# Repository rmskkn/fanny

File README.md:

# Fanny — a USB PWM fan controller

A USB-controlled carrier board for an STM32F103C8T6 "Blue Pill" module. It
drives four 12 V PC fans and reads four analog sensors. The module shows up
on the host as a USB CDC serial port (`/dev/ttyACM*` or `COMx`).

## Key features

- **4 independent fan channels.** Each one switches between `pwm` (4-pin
  signal control) and `dc` (3-pin supply chopping) at runtime.
- **4 analog inputs** for NTC or voltage sensors plus 12 V rail sensing. All
  share one ADC scan with mV conversion.
- **Tach and stall detection** on all 4 channels. Fans 1-3 are counted by
  hardware timers, fan 4 by a level-checked interrupt.
- **Hardware failsafe by design.** Every control line rests in its "fan on"
  state by default, held there by pull resistors alone. A fan runs at
  100% on power-up, after a crash, or with the MCU pulled out. No firmware
  or host required.
- **Per-channel and board-level PTC fusing** plus a 12 V TVS.
- **Text protocol over USB CDC.** Comes with a Python CLI (`fanctl.py`) and
  a daemon (`fancontrold.py`) for temperature or GPU-temperature curves.

## Repository structure

```
.
├── firmware/          MCU firmware
│   ├── Core/          clocks, SysTick, linker script, board pin map
│   ├── Drivers/       libopencm3 submodule
│   ├── USB_DEVICE/    USB CDC-ACM device
│   ├── App/           fan, pwm, tach, protocol, thermal, safety
│   └── tests/         host-side unit tests
├── hardware/
│   ├── kicad/         schematic, symbol lib, board
│   ├── bom.csv        bill of materials
│   ├── pcb_3d.png     3D render of the placed board
│   ├── pcb_top.png    placement plot seen from the top
│   └── datasheets/    links to the key datasheets
└── host/              fanctl.py command-line client (pyserial)
```

## Prerequisites

KiCad 10.0.7, arm-none-eabi-gcc, OpenOCD, and Python 3 with pyserial:

```sh
# Arch
sudo pacman -S kicad arm-none-eabi-gcc arm-none-eabi-newlib openocd python python-pyserial

# Ubuntu 24.04
sudo add-apt-repository ppa:kicad/kicad-10.0-releases
sudo apt update
sudo apt install kicad gcc-arm-none-eabi openocd python3 python3-serial
```

You also need an ST-Link V2 programmer wired to the Blue Pill's SWD header
to flash firmware.

## Hardware design

### Block overview

```mermaid
flowchart LR
    classDef power fill:#fde3d8,stroke:#e2572b,color:#111
    classDef usb fill:#dbe7ff,stroke:#2f6fed,color:#111
    classDef mcu fill:#e8d7f5,stroke:#5b4b8a,color:#111
    classDef pwm fill:#d7f5df,stroke:#2f9e44,color:#111
    classDef dcmode fill:#fdecc3,stroke:#c77f00,color:#111
    classDef tach fill:#d7f5df,stroke:#0f9b8e,color:#111
    classDef analog fill:#fbd9e8,stroke:#c2255c,color:#111

    subgraph PWR["Power 12 V"]
        PSU["12 V PSU"] --> J1["J1 Mate-N-Lok"] --> F1["F1 PTC 2.5A"] --> D1["D1 TVS"] --> V12["+12V"]
        V12 --> F25["F2..F5 1.1A PTC x4"] --> FANV["fan +12V x4"]
        V12 --> DIV["47k/10k divider"] --> PB0["PB0 ADC"]
    end

    subgraph USB3V3["USB / 3V3"]
        USB["USB via Blue Pill microB"] --> P5V["+5V"] --> LDO["Blue Pill LDO"] --> V33["+3V3"] --> FB1["FB1"] --> V33A["+3V3A"]
    end

    subgraph MCU["Blue Pill module on J2 and J3"]
        subgraph PWMSIG["PWM signal on fan pin 4"]
            TIM4["TIM4 PB6..PB9 25kHz"] --> BSS["BSS138 open drain"] --> FPWM["fan PWM pin"]
        end
        subgraph DCMODE["DC-mode motor switch per channel"]
            QINV["Q_inv BSS138"] --> QEN["Q_en gated by FANn_DCEN"] --> QPNP["Q_pnp AO3401A pull-up"] --> QHS["Q_hs AO3401A"] --> FSW["fan +12V motor switch"]
            GPIO["PA6 PA7 PA8 PB1 GPIO"] --> QEN
        end
        TIM4 -. reuses PWM signal .-> QINV
        subgraph TACHLANE["Tach"]
            FT["fan tach"] --> PU["10k pull-up"] --> RC["RC filter"] --> EXTI["TIM1/2/3 counters, EXTI PB15"]
        end
    end

    subgraph ANALOG["Analog inputs"]
        SENS["sensors"] --> RCB["1k + 100n + BAT54S"] --> ADC["PA0..PA5 ADC x6"]
    end

    class PSU,J1,F1,D1,V12,F25,FANV,DIV power
    class PB0 mcu
    class USB,P5V,LDO,V33,FB1,V33A usb
    class TIM4,BSS,FPWM pwm
    class QINV,QEN,QPNP,QHS,FSW,GPIO dcmode
    class FT,PU,RC,EXTI tach
    class SENS,RCB,ADC analog
```

### Pin map

| Function | Pins | Peripheral |
|---|---|---|
| Fan 1–4 PWM signal and the motor-switch chop signal in DC mode | PB6 PB7 PB8 PB9 | TIM4 CH1–4 at 25 kHz |
| Fan 1–4 DC-mode enable | PA6 PA7 PA8 PB1 | plain push-pull GPIO |
| Fan 1–3 tach | PA9 PA15 PB5 | TIM1 CH2, TIM2 CH1 (partial remap 1), TIM3 CH2 (partial remap), each in external clock mode counting falling edges in hardware |
| Fan 4 tach | PB15 | EXTI15 on both edges, counted only on a real high-to-low level change |
| AIN1–AIN4 | PA0–PA3 | ADC1 IN0–IN3 |
| 12 V sense | PB0 | ADC1 IN8 |

### Compatibility

Verified against the [Intel 4-wire PWM fan spec rev 1.2](https://www.konilabs.net/docs/standards/fan/intel_4wire_pwm_fans_specs_rev1_2.pdf):

| Spec requirement | Board implementation | Status |
|---|---|---|
| Pinout of GND then +12 V then tach then PWM | `Fan_4pin` header wired in that order | Match |
| PWM must be open-drain or open-collector with the fan pulling up | BSS138 open-drain transistor where the MCU only sinks | Match |
| PWM frequency between 21 kHz and 28 kHz with 25 kHz nominal | TIM4 at 72 MHz / 2880 which is exactly 25.000 kHz | Match |
| A released PWM line must run the fan at full speed | 100 kΩ pull-down holds the transistor off until firmware drives it | Match |
| Tach must be open-collector and pulled up at 2 pulses per rev | 10 kΩ pull-up to 3.3 V with `TACH_PULSES_PER_REV = 2` in firmware | Match |
| Tach pull-up rail of 5 V or less into a tolerant input | Pulled to 3.3 V. PA9, PA15 and PB15 are 5 V tolerant; PB5 is not, so fan 3 needs the 3.3 V pull-up | Match |

### Analog inputs (AIN1–AIN4)

Each input is a 3-pin header carrying 3V3A and SIG and GND. The conditioning
chain works like this:

- A 10 kΩ pull-up to 3V3A. Together with a 10 kΩ NTC to GND it forms a
  ratiometric temperature divider. Leave it unfitted for voltage-output
  sensors.
- A 1 kΩ series resistor and 100 nF to GND for anti-aliasing and sample
  charge.
- A BAT54S clamp to GND and 3V3A. PA0–PA3 are **not** 5 V tolerant.

The ADC references VDDA. The firmware measures VREFINT so it can report
millivolts corrected for the actual supply voltage.

#### Choosing an NTC

The on-board pull-up is 10 kΩ, matched to a 10 kΩ NTC with B=3950 (`ntc_r25 =
10000`, `ntc_beta = 3950` in the fan daemon config, both already the
defaults). Any bare 2-wire 10 kΩ/B3950 probe plugs straight in, SIG and GND,
no third wire needed — this is what the probe bundled with the
[Skip0ner 1X4L fan-1248 conf v1](https://skiponer.com/1x4l-pwm-fan-controller-manual/)
module is. Expected mV at a given temperature:
`hardware/datasheets/NTC-10k-B3950 Response Curve.md`, taken from the
10k/3950 column of Focusensing's
[10k thermistor reference chart](https://www.focusensing.com/10k-thermistor-chart-type-2-vs-type-3-vs-3950-tables_n196).
The onboard autocurve mode (`auto on`) uses the same table, baked into
`firmware/App/ntc_calib.h`.

A different R25 needs a matching pull-up swap, since the pull-up sets both
the divider's output range and the firmware's calibration constant: match
`ntc_r25` (host) and `ntc_calib_ain1..4` (firmware) to the new part's R25 and
B, and re-check `fanctl.py get`'s `ain N mv` against a known temperature
before trusting the curve.

### Power

- **12 V input:** a screw terminal followed by a PTC that holds 2.5 A and
  then an SMBJ13A TVS. Reversed polarity makes the TVS conduct and that trips
  the PTC.
- **Module supply:** USB only. The board carries no 5 V or 3.3 V regulator.
  The LDO on the Blue Pill makes 3.3 V from USB VBUS.
- **12 V monitoring:** a 47 kΩ/10 kΩ divider into PB0. Full scale lands near
  18.8 V.
- **USB:** the micro-B connector of the Blue Pill and nothing else. The
  carrier has no USB connector or header or ESD protection of its own. The
  firmware pulls D+ low for 10 ms at boot to force the host to re-enumerate.

## BOM list

The full bill of materials is in [`hardware/bom.csv`](hardware/bom.csv).

## Firmware

### Build

```sh
git clone --recurse-submodules git@github.com:rmskkn/fanny.git
cd fanny
make                 # firmware/build/fanny.elf, .bin (~11.5 KiB flash)
make flash           # flash fanny.bin, OpenOCD + ST-Link over SWD
make test            # host-side protocol and conversion tests
```

The first `make` builds libopencm3 for STM32F1 only. It also runs
`git submodule update --init` when the clone has no submodule checkout. The
same targets work from inside `firmware/`.

`make flash` wraps this OpenOCD call, with an ST-Link programmer on the
Blue Pill's SWD header. `fanny.bin` is a raw image with no load address, so
one is given on the command line, the start of flash on this MCU:

```sh
openocd -f interface/stlink.cfg -f target/stm32f1x.cfg \
    -c "program firmware/build/fanny.bin verify reset exit 0x08000000"
```

`fanny.elf` still builds alongside it (`make` keeps producing both), kept
for `arm-none-eabi-size` and debugging, but flashing only ever needs the bin.

### Failsafe behaviour

All fans run at 100 % whenever the controller is not in control and that holds
in both `pwm` and `dc` mode. Fan power comes straight from 12 V so this needs
nothing but 12 V present. The PWM signal line and the motor switch and the
DC-mode enable all rest in their "fan on" state. Pin 4 is released and
`R_gpd` holds the motor switch on and `R_dcen` holds the enable off. Either
mode reaches 100 % the same way.

| Case | Result |
|---|---|
| Power-up before the first command from the host | 100 % |
| USB unplugged or host powered off | Module unpowered and both switches rest on at 100 % |
| Module pulled out of its socket | Both switches rest on at 100 % |
| Supply sags below the reset threshold of the STM32 near 1.9 V | MCU held in reset and both switches rest on at 100 % |
| Firmware hangs | Watchdog resets the MCU after 1 s and both switches rest on during reset at 100 % |
| No valid command for 10 s while the module is still powered | Firmware failsafe sets 100 % and the LED blinks fast and the mode stays unchanged |

Running `fanctl.py watch` or a control daemon keeps the 10 s timer from
expiring. A fan is flagged `stall=1` when its duty sits above 0 but its tach
reads 0 RPM for 3 s. Fans without a tach wire always show this flag.

### Host commands

The protocol is text over USB CDC and the baud rate is ignored. Each command
is one line ending in `\n` and each reply ends with `ok` or `err <reason>`.

```
> set 2 40          duty 0..100 for fan 1..4 or "all"
ok
> mode 3 dc         pwm (4-pin) | dc (3-pin)
ok
> get
fan 1 mode=pwm duty=100 rpm=1590 stall=0
fan 2 mode=pwm duty=40 rpm=780 stall=0
fan 3 mode=dc duty=100 rpm=1200 stall=0
fan 4 mode=pwm duty=100 rpm=0 stall=1
ain 1 raw=2047 mv=1649
...
v12 mv=12043
vdda mv=3302
mcu temp=31.4
failsafe=0
ok
> ping              keepalive
ok
```

## Host tool

```sh
pip install -r host/requirements.txt
python3 host/fanctl.py -p /dev/ttyACM0 get
python3 host/fanctl.py set all 50
python3 host/fanctl.py mode 3 dc
python3 host/fanctl.py watch -i 2
```

### Setting one fan

Use the fan number from 1 to 4 in place of `all`. Fan 1 is header J5 and fan
4 is header J8.

```sh
python3 host/fanctl.py set 1 50      # fan 1 to 50 %
python3 host/fanctl.py set 3 80      # fan 3 to 80 %
python3 host/fanctl.py set 4 0       # fan 4 to 0 % (some fans keep turning slowly)
python3 host/fanctl.py -p /dev/ttyACM1 set 2 40   # board on another port
```

- Each command sets one fan or all fans. Lists such as `1,2` and ranges such
  as `1-3` are not accepted.
- To check a fan run `python3 host/fanctl.py get` and read the
  `fan N mode=... duty=... rpm=...` line.
- Settings hold only while the host keeps talking to the board. When no
  command arrives for 10 s all fans return to 100 %. Keep `fanctl.py watch`
  or a control daemon running to hold the values.
- `mode <1-4|all> pwm|dc` picks the speed-control path for a channel: `pwm`
  for a 4-pin fan, `dc` for a 3-pin fan. It falls back to `pwm` at every
  boot and after every reconnect so the channel of a 3-pin fan needs
  `mode N dc` sent again each time.

The `FanController` class in `fanctl.py` can be imported to build a control
daemon. One example is a daemon that maps an NTC reading from `ain` onto a fan
duty. For a 10 kΩ NTC sitting on the 10 kΩ bias resistor the resistance is
R<sub>NTC</sub> = 10 kΩ × mV / (VDDA − mV).

### Fan control daemon

`host/fancontrold.py` is exactly that daemon. It reads an INI config shown in
`host/fancontrol.conf.example`. The config can set each of the four channels
to a constant duty or to a temperature curve driven by one AIN input or to a
curve driven by the temperature of an NVIDIA GPU through `sensor = gpuN` read
via `nvidia-smi` using the higher of the core and memory temperature. A
managed channel also takes `type = pwm` for the 4-pin default or `type = dc`
for a 3-pin fan. The daemon sends `mode` once at startup and again after every
reconnect because a firmware reset returns every channel to `pwm`. Every cycle
it re-sends the duty of each managed channel which doubles as the ping that
holds off the 10 s firmware failsafe. A channel with no `[fanN]` section is
left alone. `nvidia-smi` must be on `PATH` and no extra Python dependency is
needed.

For a `gpuN` sensor install the proprietary NVIDIA driver which provides
`nvidia-smi`:

```sh
# Arch
sudo pacman -S nvidia nvidia-utils

# Ubuntu 24.04
sudo apt install nvidia-driver-550
```

Reboot the machine to load the nvidia modules. Verify with
`nvidia-smi --query-gpu=index,temperature.gpu,temperature.memory --format=csv`.

```sh
cp host/fancontrol.conf.example ~/.config/fancontrol.conf
# edit ~/.config/fancontrol.conf for your sensors and curves
python3 host/fancontrold.py                 # foreground, Ctrl-C to stop
```

To run it as a systemd user service:

```sh
mkdir -p ~/.config/systemd/user
cp host/systemd/fancontrold.service ~/.config/systemd/user/
# edit ExecStart in that file to this repo's checkout path
systemctl --user daemon-reload
systemctl --user enable --now fancontrold.service
loginctl enable-linger "$USER"   # only if the board must run with no user session logged in
```

## Known limits

- **0 % doesn't stop every 4-pin fan in `pwm` mode** (fan-dependent). It does
  stop the fan in `dc` mode.
- **Duty 1-100 % maps to 10-100 % on the PWM line.** A Noctua NF-P12 PWM
  won't start below 10 % and stops below about 6 % even after a spin-up, so
  the firmware never sends less than 10 % unless you set 0 %. At 1 % that fan
  runs at about 200 rpm. Every other setting lands a little above its raw
  value: 50 % sends 55 %.
- **3-pin fans in `dc` mode won't start below ~30-40 % duty** (motor limit,
  not firmware). Set a curve minimum above it.
- **Fan 4 tach uses an interrupt, not a hardware counter.** Each counter
  needs a whole timer, and the STM32F103C8 has four: TIM1-TIM3 count fans
  1-3 and TIM4 makes the PWM. Fan 4 runs on EXTI15 with a pin-level check
  that ignores spikes shorter than the interrupt entry time (about 0.5 us).
  Longer glitches still count, and edges closer together than the handler
  runtime can merge.
- **JTAG is off** because fan 2 tach uses PA15. SWD on PA13/PA14 still
  flashes and debugs the board.
- **Tach under-reads in `dc` mode** since the fan is unpowered during the
  chopped-off phase. `stall` is only meaningful near 100 % duty.
- **25 kHz chop stresses a fan's input cap** but stays inaudible. All four
  `pwm` channels share one chop frequency.

## License

Copyright © 2026 Roman Skakun.

This project covers the hardware design files and the firmware and the host
tool. All of it is licensed under
[Creative Commons Attribution-NonCommercial-ShareAlike 4.0 International](LICENSE)
which is CC BY-NC-SA 4.0.

You may build and modify and share this design for personal and other
non-commercial purposes with attribution and under the same license.
Commercial use is not permitted without a separate written license from the
copyright holder. That includes selling assembled boards or bare PCBs or kits.

`firmware/Drivers/libopencm3` is a submodule under its own LGPL-3.0 license
and is not covered by the above.

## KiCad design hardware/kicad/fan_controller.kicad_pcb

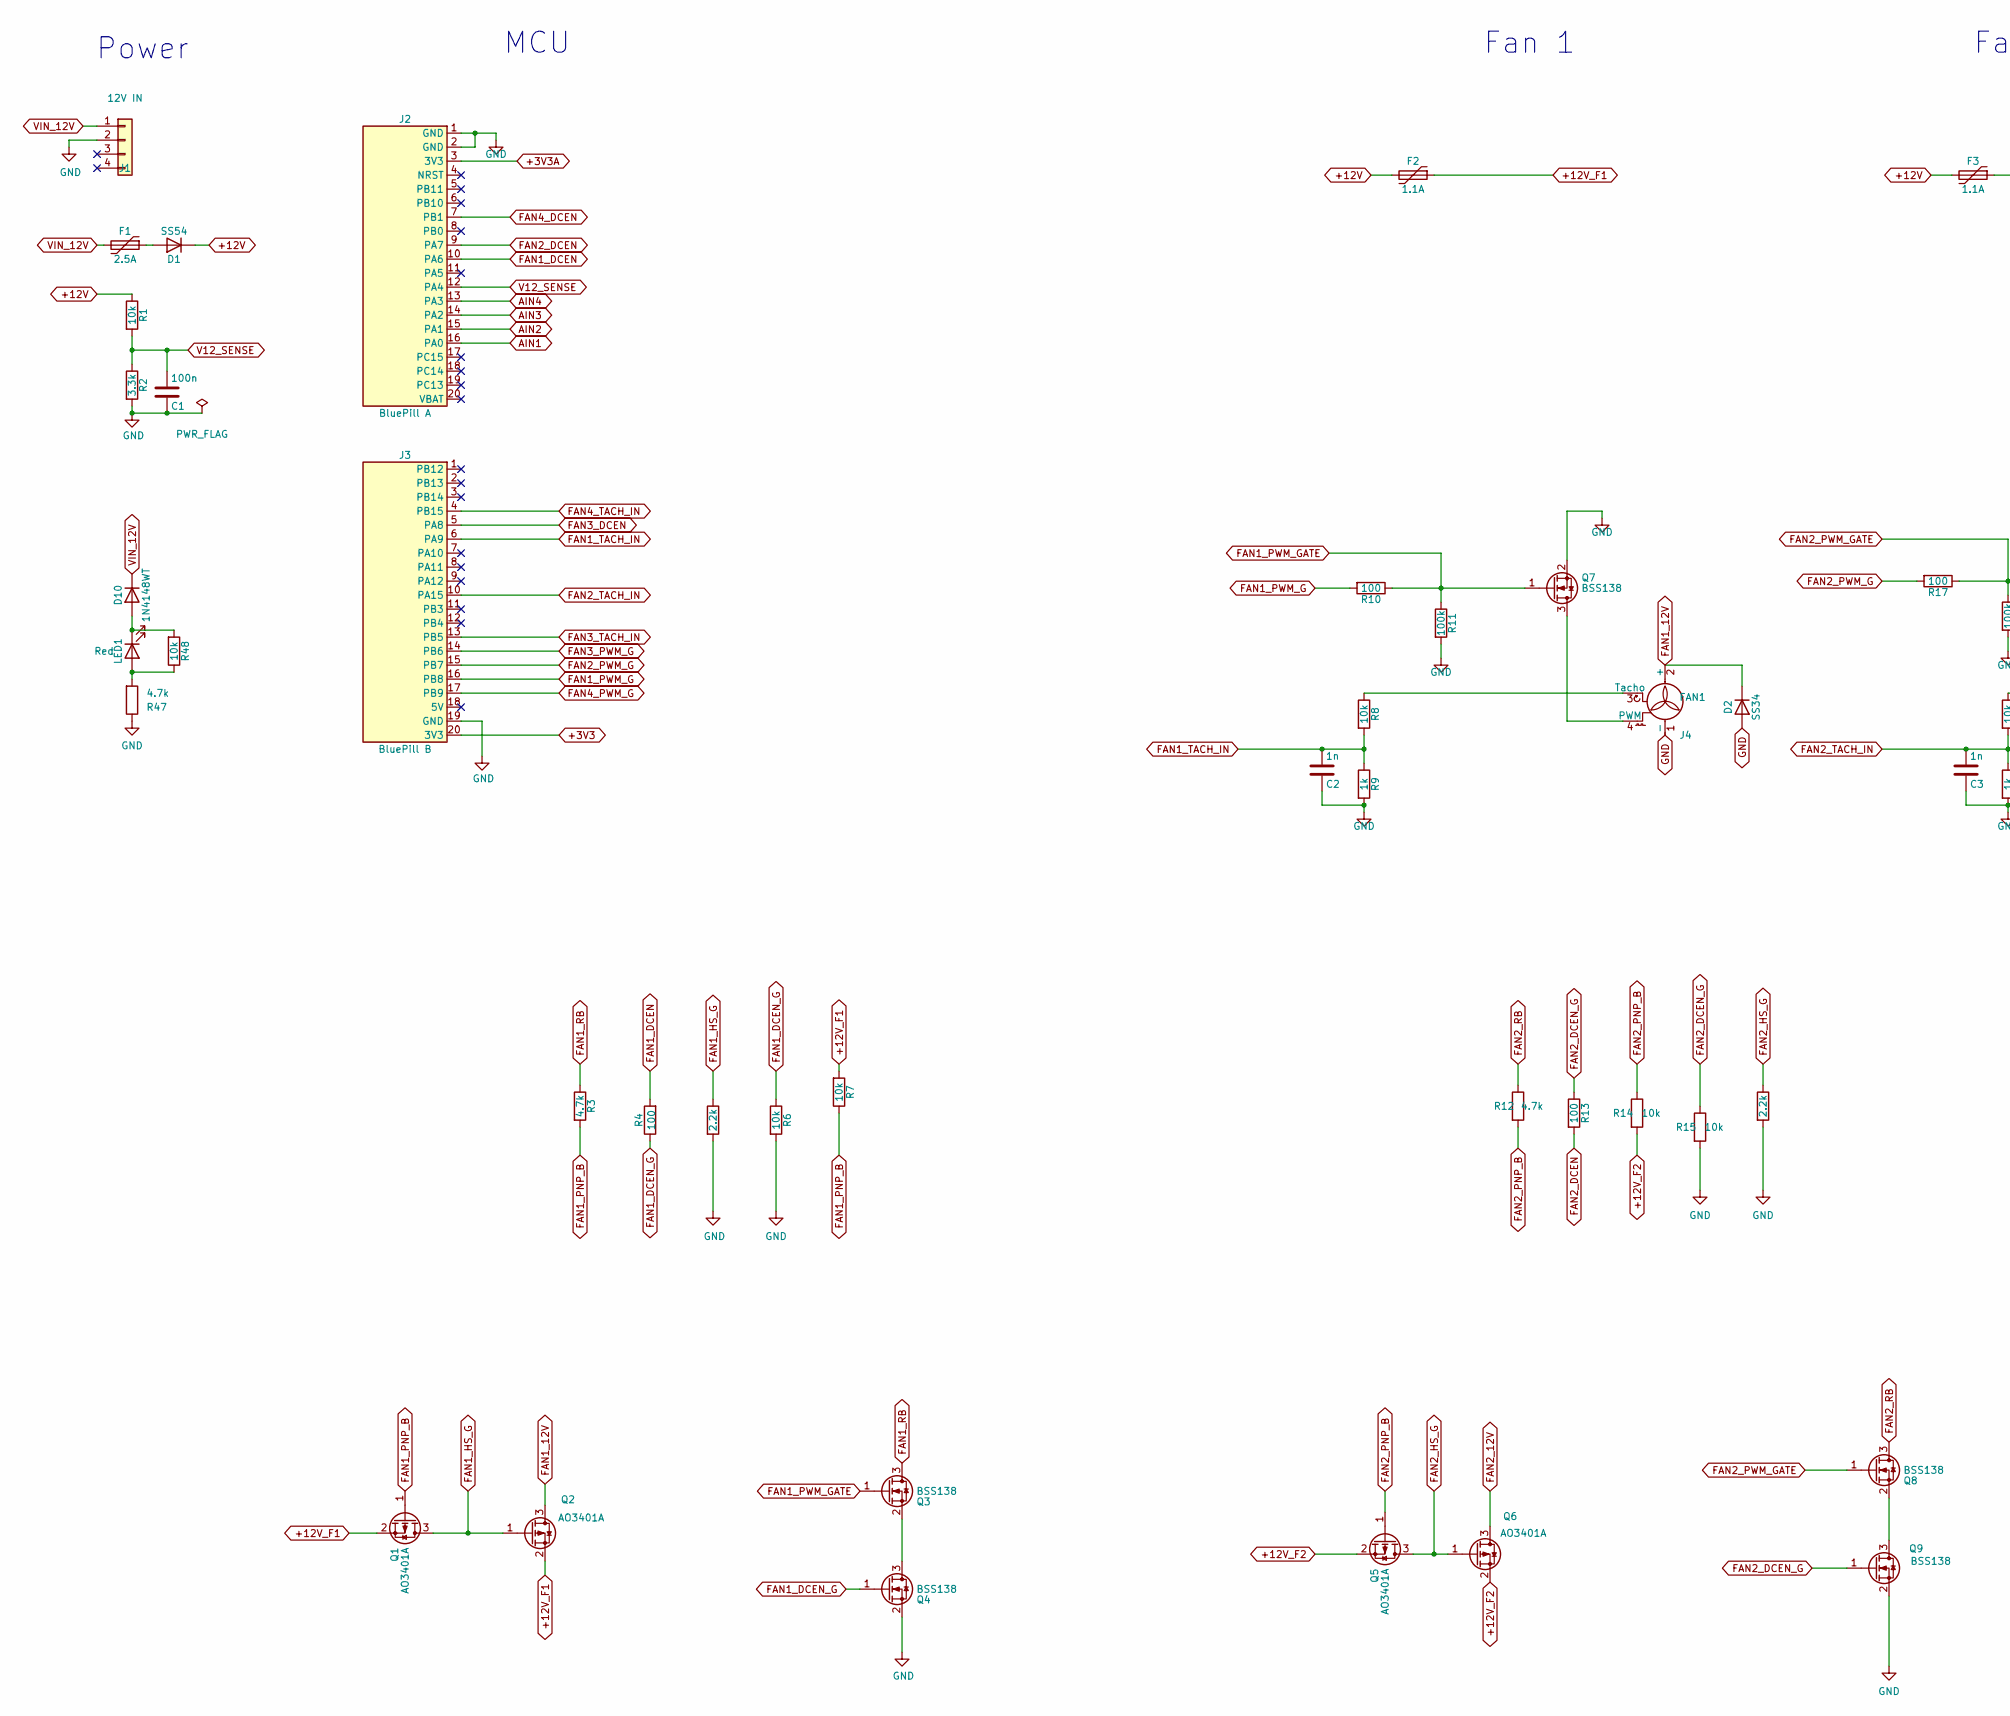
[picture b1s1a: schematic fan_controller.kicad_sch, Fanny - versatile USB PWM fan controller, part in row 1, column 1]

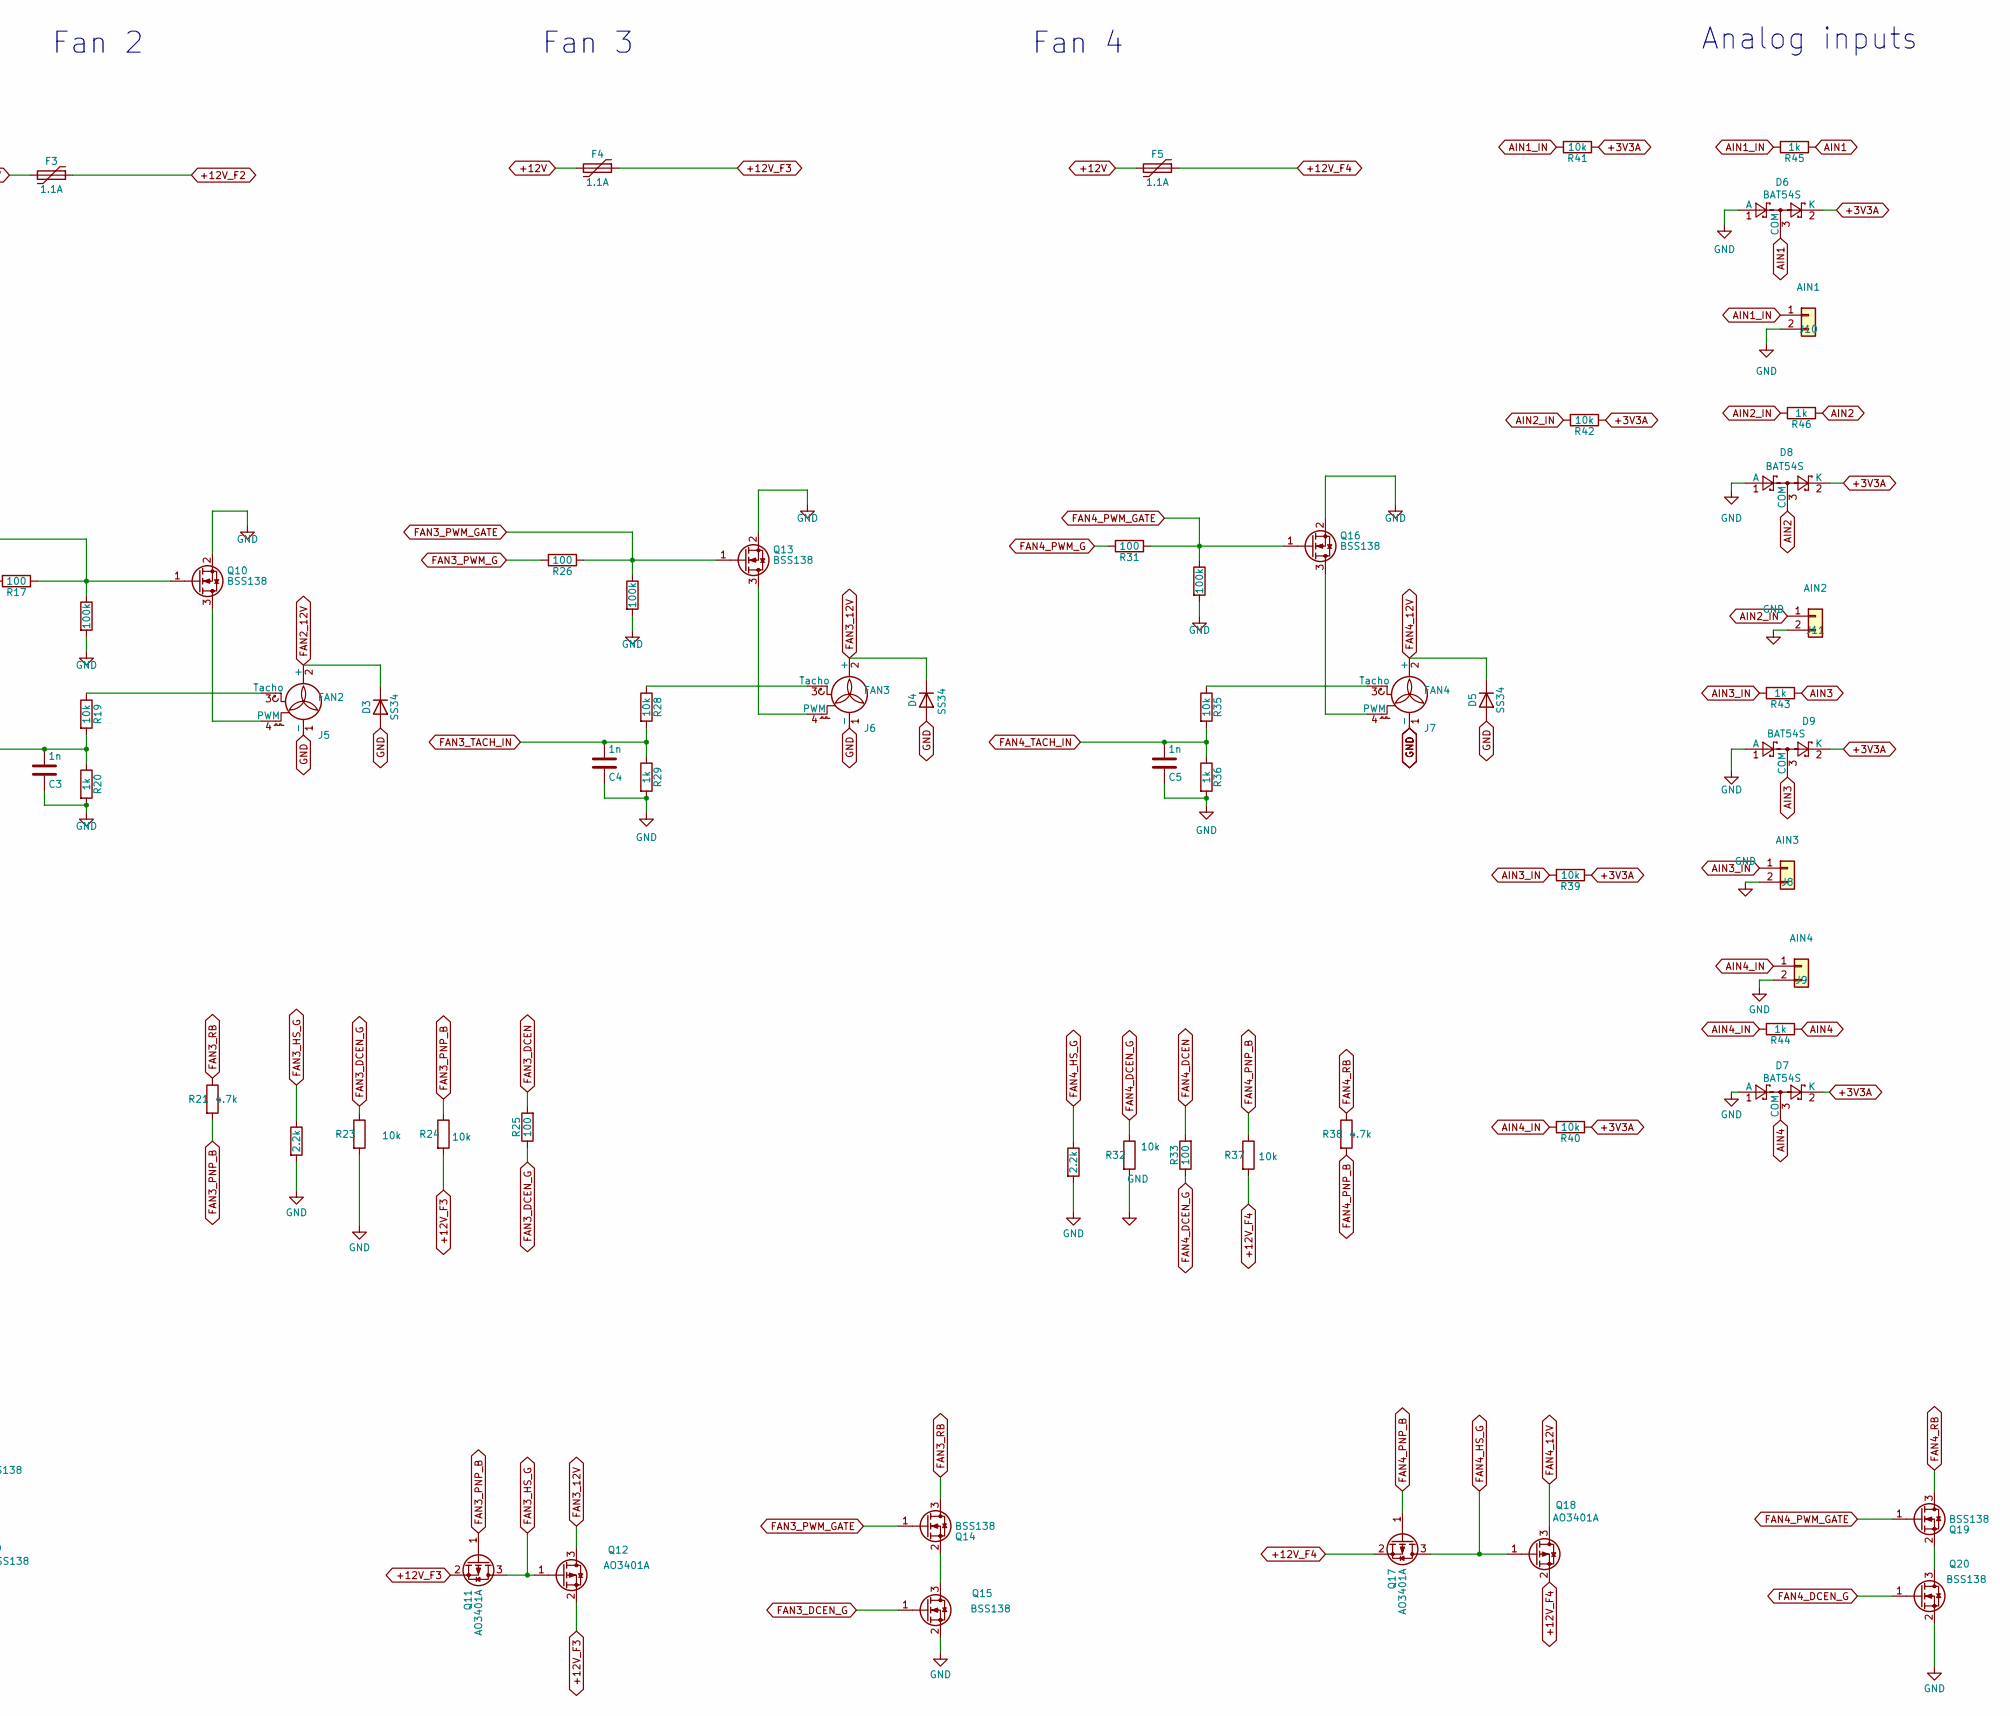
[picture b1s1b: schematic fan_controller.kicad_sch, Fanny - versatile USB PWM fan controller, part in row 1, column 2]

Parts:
C1: 100n; C_0603_1608Metric
C2, C3, C4, C5: 1n; C_0603_1608Metric
D1: SS54; D_SMB; MPN Littelfuse SMBJ13A
D2, D3, D4, D5: SS34; D_SMA; MPN SS34
D6, D7, D8, D9: BAT54S; SOT-23; MPN Nexperia BAT54S,215
D10: 1N4148WT; D_SOD-523
F1: 2.5A; Fuse_1812_4532Metric; MPN Bourns MF-MSMF250/16X-2
F2, F3, F4, F5: 1.1A; Fuse_1812_4532Metric; MPN Bourns MF-MSMF110/16-2
J1: 12V IN; ConnHeader_MateNLok_1x04_P5.08mm_Vertical; MPN TE Connectivity 350424-1
J2: BluePill A; PinSocket_1x20_P2.54mm_Vertical
J3: BluePill B; PinSocket_1x20_P2.54mm_Vertical
J4: FAN1; FanPinHeader_1x04_P2.54mm_Vertical; MPN Molex 47053-1000
J5: FAN2; FanPinHeader_1x04_P2.54mm_Vertical; MPN Molex 47053-1000
J6: FAN3; FanPinHeader_1x04_P2.54mm_Vertical; MPN Molex 47053-1000
J7: FAN4; FanPinHeader_1x04_P2.54mm_Vertical; MPN Molex 47053-1000
J8: AIN3; JST_PH_B2B-PH-K_1x02_P2.00mm_Vertical
J9: AIN4; JST_PH_B2B-PH-K_1x02_P2.00mm_Vertical
J10: AIN1; JST_PH_B2B-PH-K_1x02_P2.00mm_Vertical
J11: AIN2; JST_PH_B2B-PH-K_1x02_P2.00mm_Vertical
LED1: Red; LED_0603_1608Metric
Q1, Q2, Q5, Q6, Q11, Q12, Q17, Q18: AO3401A; SOT-23; MPN Alpha & Omega AO3401A
Q3, Q7, Q8, Q10, Q13, Q14, Q16, Q19: BSS138; SOT-23; MPN onsemi BSS138
Q4, Q9, Q15, Q20: BSS138; SOT-23
R1, R6, R7, R8, R14, R15, R19, R23, R24, R28, R32, R35, R37, R39, R40, R41, R42, R48: 10k; R_0603_1608Metric
R2: 3.3k; R_0603_1608Metric
R3, R12, R21, R38: 4.7k; R_0603_1608Metric
R4, R10, R13, R17, R25, R26, R31, R33: 100; R_0603_1608Metric
R5, R16, R22, R30: 2.2k; R_0603_1608Metric
R9, R20, R29, R36, R43, R44, R45, R46: 1k; R_0603_1608Metric
R11, R18, R27, R34: 100k; R_0603_1608Metric
R47: 4.7k; R_1206_3216Metric

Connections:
+3V3: J3.20 (3V3); also elsewhere on the board
+3V3A: D6.2 (K), D7.2 (K), D8.2 (K), D9.2 (K), J2.3 (3V3), R39.1, R40.1, R41.1, R42.1; also elsewhere on the board
+12V: D1.1 (K), F2.2, F3.2, F4.2, F5.2, R1.1
+12V_F1: F2.1, Q1.2 (S), Q2.2 (S), R7.2
+12V_F2: F3.1, Q5.2 (S), Q6.2 (S), R14.2
+12V_F3: F4.1, Q11.2 (S), Q12.2 (S), R24.2
+12V_F4: F5.1, Q17.2 (S), Q18.2 (S), R37.2
AIN1: D6.3 (COM), J2.16 (PA0), R45.1
AIN1_IN: J10.1, R41.2, R45.2
AIN2: D8.3 (COM), J2.15 (PA1), R46.1
AIN2_IN: J11.1, R42.2, R46.2
AIN3: D9.3 (COM), J2.14 (PA2), R43.1
AIN3_IN: J8.1, R39.2, R43.2
AIN4: D7.3 (COM), J2.13 (PA3), R44.1
AIN4_IN: J9.1, R40.2, R44.2
FAN1_12V: D2.1 (K), J4.2 (+), Q2.3 (D)
FAN1_DCEN: J2.10 (PA6), R4.2
FAN1_DCEN_G: Q4.1 (G), R4.1, R6.1
FAN1_HS_G: Q1.3 (D), Q2.1 (G), R5.1
FAN1_PNP_B: Q1.1 (G), R3.2, R7.1
FAN1_PWM_G: J3.16 (PB8), R10.2
FAN1_PWM_GATE: Q3.1 (G), Q7.1 (G), R10.1, R11.1
FAN1_RB: Q3.3 (D), R3.1
FAN1_TACH_IN: C2.1, J3.6 (PA9), R8.2, R9.1; also elsewhere on the board
FAN2_12V: D3.1 (K), J5.2 (+), Q6.3 (D)
FAN2_DCEN: J2.9 (PA7), R13.2
FAN2_DCEN_G: Q9.1 (G), R13.1, R15.1
FAN2_HS_G: Q5.3 (D), Q6.1 (G), R16.1
FAN2_PNP_B: Q5.1 (G), R12.2, R14.1
FAN2_PWM_G: J3.15 (PB7), R17.2
FAN2_PWM_GATE: Q8.1 (G), Q10.1 (G), R17.1, R18.1
FAN2_RB: Q8.3 (D), R12.1
FAN2_TACH_IN: C3.1, J3.10 (PA15), R19.2, R20.1; also elsewhere on the board
FAN3_12V: D4.1 (K), J6.2 (+), Q12.3 (D)
FAN3_DCEN: J3.5 (PA8), R25.2
FAN3_DCEN_G: Q15.1 (G), R23.1, R25.1
FAN3_HS_G: Q11.3 (D), Q12.1 (G), R22.1
FAN3_PNP_B: Q11.1 (G), R21.2, R24.1
FAN3_PWM_G: J3.14 (PB6), R26.2
FAN3_PWM_GATE: Q13.1 (G), Q14.1 (G), R26.1, R27.1
FAN3_RB: Q14.3 (D), R21.1
FAN3_TACH_IN: C4.1, J3.13 (PB5), R28.2, R29.1; also elsewhere on the board
FAN4_12V: D5.1 (K), J7.2 (+), Q18.3 (D)
FAN4_DCEN: J2.7 (PB1), R33.2
FAN4_DCEN_G: Q20.1 (G), R32.1, R33.1
FAN4_HS_G: Q17.3 (D), Q18.1 (G), R30.1
FAN4_PNP_B: Q17.1 (G), R37.1, R38.2
FAN4_PWM_G: J3.17 (PB9), R31.2
FAN4_PWM_GATE: Q16.1 (G), Q19.1 (G), R31.1, R34.1
FAN4_RB: Q19.3 (D), R38.1
FAN4_TACH_IN: C5.1, J3.4 (PB15), R35.2, R36.1; also elsewhere on the board
GND: C1.2, C2.2, C3.2, C4.2, C5.2, D2.2 (A), D3.2 (A), D4.2 (A), D5.2 (A), D6.1 (A), D7.1 (A), D8.1 (A), D9.1 (A), J1.2, J2.1 (GND), J2.2 (GND), J3.19 (GND), J4.1 (-), J5.1 (-), J6.1 (-), J7.1 (-), J8.2, J9.2, J10.2, J11.2, Q4.2 (S), Q7.2 (S), Q9.2 (S), Q10.2 (S), Q13.2 (S), Q15.2 (S), Q16.2 (S), Q20.2 (S), R2.2, R5.2, R6.2, R9.2, R11.2, R15.2, R16.2, R18.2, R20.2, R22.2, R23.2, R27.2, R29.2, R30.2, R32.2, R34.2, R36.2, R47.1; also elsewhere on the board
unnamed: D1.2 (A), F1.1
unnamed: D10.2 (A), LED1.1 (K), R48.2
unnamed: J4.4 (PWM), Q7.3 (D)
unnamed: J4.3 (Tacho), R8.1
unnamed: J5.4 (PWM), Q10.3 (D)
unnamed: J5.3 (Tacho), R19.1
unnamed: J6.4 (PWM), Q13.3 (D)
unnamed: J6.3 (Tacho), R28.1
unnamed: J7.4 (PWM), Q16.3 (D)
unnamed: J7.3 (Tacho), R35.1
unnamed: LED1.2 (A), R47.2, R48.1
unnamed: Q3.2 (S), Q4.3 (D)
unnamed: Q8.2 (S), Q9.3 (D)
unnamed: Q14.2 (S), Q15.3 (D)
unnamed: Q19.2 (S), Q20.3 (D)
V12_SENSE: C1.1, J2.12 (PA4), R1.2, R2.1
VIN_12V: D10.1 (K), F1.2, J1.1

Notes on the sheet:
Analog inputs
Power
Fan 3
MCU
Fan 2
Fan 1
Fan 4

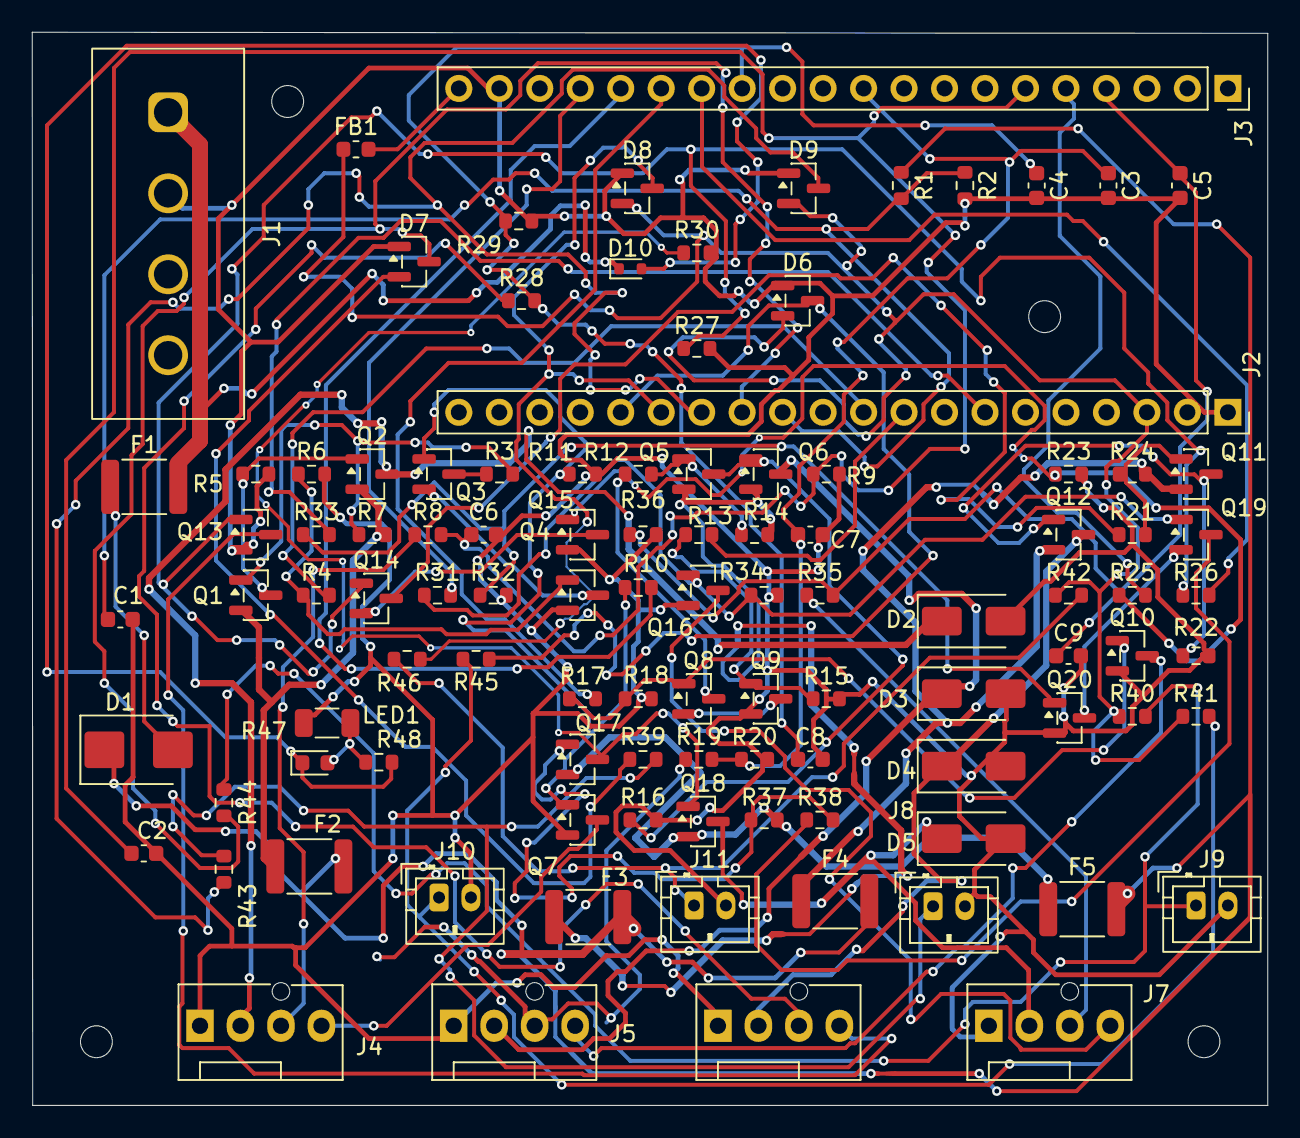
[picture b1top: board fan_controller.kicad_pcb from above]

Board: 2 copper layers, 77.5 x 67.3 mm, 109 parts (0 on the bottom side), 69 nets.

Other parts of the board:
C6, C7, C8, C9: 1n; C_0603_1608Metric
FB1: 600R@100MHz; L_0603_1608Metric
MH1, MH2, MH3, MH4: MountingHole_2mm

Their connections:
+3V3: FB1.2; also elsewhere on the board
+3V3A: FB1.1; also elsewhere on the board
FAN1_TACH_IN: C6.1; also elsewhere on the board
FAN2_TACH_IN: C7.1; also elsewhere on the board
FAN3_TACH_IN: C8.1; also elsewhere on the board
FAN4_TACH_IN: C9.1; also elsewhere on the board
GND: C6.2, C7.2, C8.2, C9.2; also elsewhere on the board

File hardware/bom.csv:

Qty,References,Value,Footprint,MPN (example),DigiKey PN,DigiKey URL,Notes,DNP
1,C1,100n,C_0603_1608Metric,Yageo CC0603KRX7R9BB104,311-1344-2-ND,https://www.digikey.com/en/products/detail/yageo/CC0603KRX7R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,,
4,C2 C3 C4 C5,1n,C_0603_1608Metric,Yageo CC0603KRX7R9BB102,311-1080-2-ND,https://www.digikey.com/en/products/detail/yageo/CC0603KRX7R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,,
1,D1,SMBJ13A,D_SMB,Littelfuse SMBJ13A,SMBJ13ALFTR-ND,https://www.digikey.com/en/products/detail/littelfuse-inc/SM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,,
4,D2 D3 D4 D5,SS34,D_SMA,SMC Diode Solutions SS34AF,1655-SS34AFTR-ND,https://www.digikey.com/en/products/detail/smc-diode-solutio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,,
4,D6 D7 D8 D9,BAT54S,SOT-23,"Nexperia BAT54S,215",1727-2904-2-ND,https://www.digikey.com/en/products/detail/nexperia-usa-inc/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,,
1,F1,2.5A,Fuse_1812_4532Metric,Bourns MF-MSMF250/16X-2,MF-MSMF250/16X-2TR-ND,https://www.digikey.com/en/products/detail/bourns-inc/MF-MSM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,,
4,F2 F3 F4 F5,1.1A,Fuse_1812_4532Metric,Bourns MF-MSMF110/16-2,MF-MSMF110/16-2TR-ND,https://www.digikey.com/en/products/detail/bourns-inc/MF-MSM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,"Bourns marks this Not For New Designs (in stock, fine for prototype)",
1,J1,12V IN,ConnHeader_MateNLok_1x04_P5.08mm_Vertical,On-Shore Technology OSTOQ045450,ED2845-ND,https://www.digikey.com/en/products/detail/on-shore-technolo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,,
1,J2,BluePill A,PinSocket_1x20_P2.54mm_Vertical,Sullins PPTC201LFBN-RC,S7018-ND,https://www.digikey.com/en/products/detail/sullins-connector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,,
1,J3,BluePill B,PinSocket_1x20_P2.54mm_Vertical,Sullins PPTC201LFBN-RC,S7018-ND,https://www.digikey.com/en/products/detail/sullins-connector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,,
1,J4,FAN1,FanPinHeader_1x04_P2.54mm_Vertical,Molex 47053-1000,WM4330-ND,https://www.digikey.com/en/products/detail/molex/0470531000/2421261,,
1,J5,FAN2,FanPinHeader_1x04_P2.54mm_Vertical,Molex 47053-1000,WM4330-ND,https://www.digikey.com/en/products/detail/molex/0470531000/2421261,,
1,J6,FAN3,FanPinHeader_1x04_P2.54mm_Vertical,Molex 47053-1000,WM4330-ND,https://www.digikey.com/en/products/detail/molex/0470531000/2421261,,
1,J7,FAN4,FanPinHeader_1x04_P2.54mm_Vertical,Molex 47053-1000,WM4330-ND,https://www.digikey.com/en/products/detail/molex/0470531000/2421261,,
1,J8,AIN3,PinHeader_1x03_P2.54mm_Vertical,Sullins PRPC003SAAN-RC,35-PRPC003SAAN-RC-ND,https://www.digikey.com/en/products/detail/sullins-connector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,,
1,J9,AIN4,PinHeader_1x03_P2.54mm_Vertical,Sullins PRPC003SAAN-RC,35-PRPC003SAAN-RC-ND,https://www.digikey.com/en/products/detail/sullins-connector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,,
1,J10,AIN1,PinHeader_1x03_P2.54mm_Vertical,Sullins PRPC003SAAN-RC,35-PRPC003SAAN-RC-ND,https://www.digikey.com/en/products/detail/sullins-connector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,,
1,J11,AIN2,PinHeader_1x03_P2.54mm_Vertical,Sullins PRPC003SAAN-RC,35-PRPC003SAAN-RC-ND,https://www.digikey.com/en/products/detail/sullins-connector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,,
8,Q1 Q2 Q5 Q6 Q11 Q12 Q17 Q18,AO3401A,SOT-23,Alpha & Omega AO3401A,785-1001-2-ND,https://www.digikey.com/en/products/detail/alpha-omega-semic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,Not MMBT3906 - that part is no longer used,
12,Q3 Q4 Q7 Q8 Q9 Q10 Q13 Q14 Q15 Q16 Q19 Q20,BSS138,SOT-23,MCC BSS138-TP,BSS138-TPMSTR-ND,https://www.digikey.com/en/products/detail/mcc-micro-commerc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,,
13,R1 R6 R7 R8 R14 R15 R19 R23 R24 R28 R32 R35 R37,10k,R_0603_1608Metric,Vishay Dale CRCW060310K0FKEA,541-10.0KHTR-ND,https://www.digikey.com/en/products/detail/vishay-dale/CRCW0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,,
1,R2,3.3k,R_0603_1608Metric,Vishay Dale CRCW06033K30FKEA,541-3.30KHTR-ND,https://www.digikey.com/en/products/detail/vishay-dale/CRCW0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,,
4,R3 R12 R21 R38,4.7k,R_0603_1608Metric,Yageo RC0603FR-074K7L,311-4.70KHRTR-ND,https://www.digikey.com/en/products/detail/yageo/RC0603FR-07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,,
8,R4 R10 R13 R17 R25 R26 R31 R33,100,R_0603_1608Metric,Vishay Dale CRCW0603100RFKEA,541-100HTR-ND,https://www.digikey.com/en/products/detail/vishay-dale/CRCW0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,,
4,R5 R16 R22 R30,2.2k,R_0603_1608Metric,Yageo RC0603FR-072K2L,311-2.20KHRTR-ND,https://www.digikey.com/en/products/detail/yageo/RC0603FR-07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,,
8,R9 R20 R29 R36 R43 R44 R45 R46,1k,R_0603_1608Metric,Vishay Dale CRCW06031K00FKEA,541-1.00KHTR-ND,https://www.digikey.com/en/products/detail/vishay-dale/CRCW0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,,
4,R11 R18 R27 R34,100k,R_0603_1608Metric,Vishay Dale CRCW0603100KFKEA,541-100KHTR-ND,https://www.digikey.com/en/products/detail/vishay-dale/CRCW0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,,
4,R39 R40 R41 R42,33k,R_0603_1608Metric,Vishay Dale CRCW060333K0FKEA,541-33.0KHTR-ND,https://www.digikey.com/en/products/detail/vishay-dale/CRCW0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,,

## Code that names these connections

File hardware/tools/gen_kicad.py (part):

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def two_pin(a="~", b="~"):
    return dict(left=[("1", a)], right=[("2", b)], w=2 * G, names=a != "~")

BLUEPILL_A = ["GND", "GND", "3V3", "NRST", "PB11", "PB10", "PB1", "PB0", "PA7", "PA6",
              "PA5", "PA4", "PA3", "PA2", "PA1", "PA0", "PC15", "PC14", "PC13", "VBAT"]
BLUEPILL_B = ["PB12", "PB13", "PB14", "PB15", "PA8", "PA9", "PA10", "PA11", "PA12", "PA15",
              "PB3", "PB4", "PB5", "PB6", "PB7", "PB8", "PB9", "5V", "GND", "3V3"]

SYMBOLS = {
    "R": two_pin(),
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B = "MCU"
bluepill = {
    "GND": "GND", "3V3": "+3V3", "5V": "+5V", "NRST": "NRST",
    "PA0": "AIN1", "PA1": "AIN2", "PA2": "AIN3", "PA3": "AIN4", "PA4": "AIN5", "PA5": "AIN6",
    "PB0": "V12_SENSE", "PA11": "USB_DM", "PA12": "USB_DP",
    "PB6": "FAN1_PWM", "PB7": "FAN2_PWM", "PB8": "FAN3_PWM", "PB9": "FAN4_PWM",
    "PB12": "FAN1_TACH", "PB13": "FAN2_TACH", "PB14": "FAN3_TACH", "PB15": "FAN4_TACH",
}
for row, names in (("A", BLUEPILL_A), ("B", BLUEPILL_B)):
    part(B, f"BluePill_{row}", f"BluePill {row}", FP_SOCKET20,
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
